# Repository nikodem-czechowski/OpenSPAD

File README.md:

# OpenSPAD
My implementation of the OpenSPAD based on the design by GaudiLabs

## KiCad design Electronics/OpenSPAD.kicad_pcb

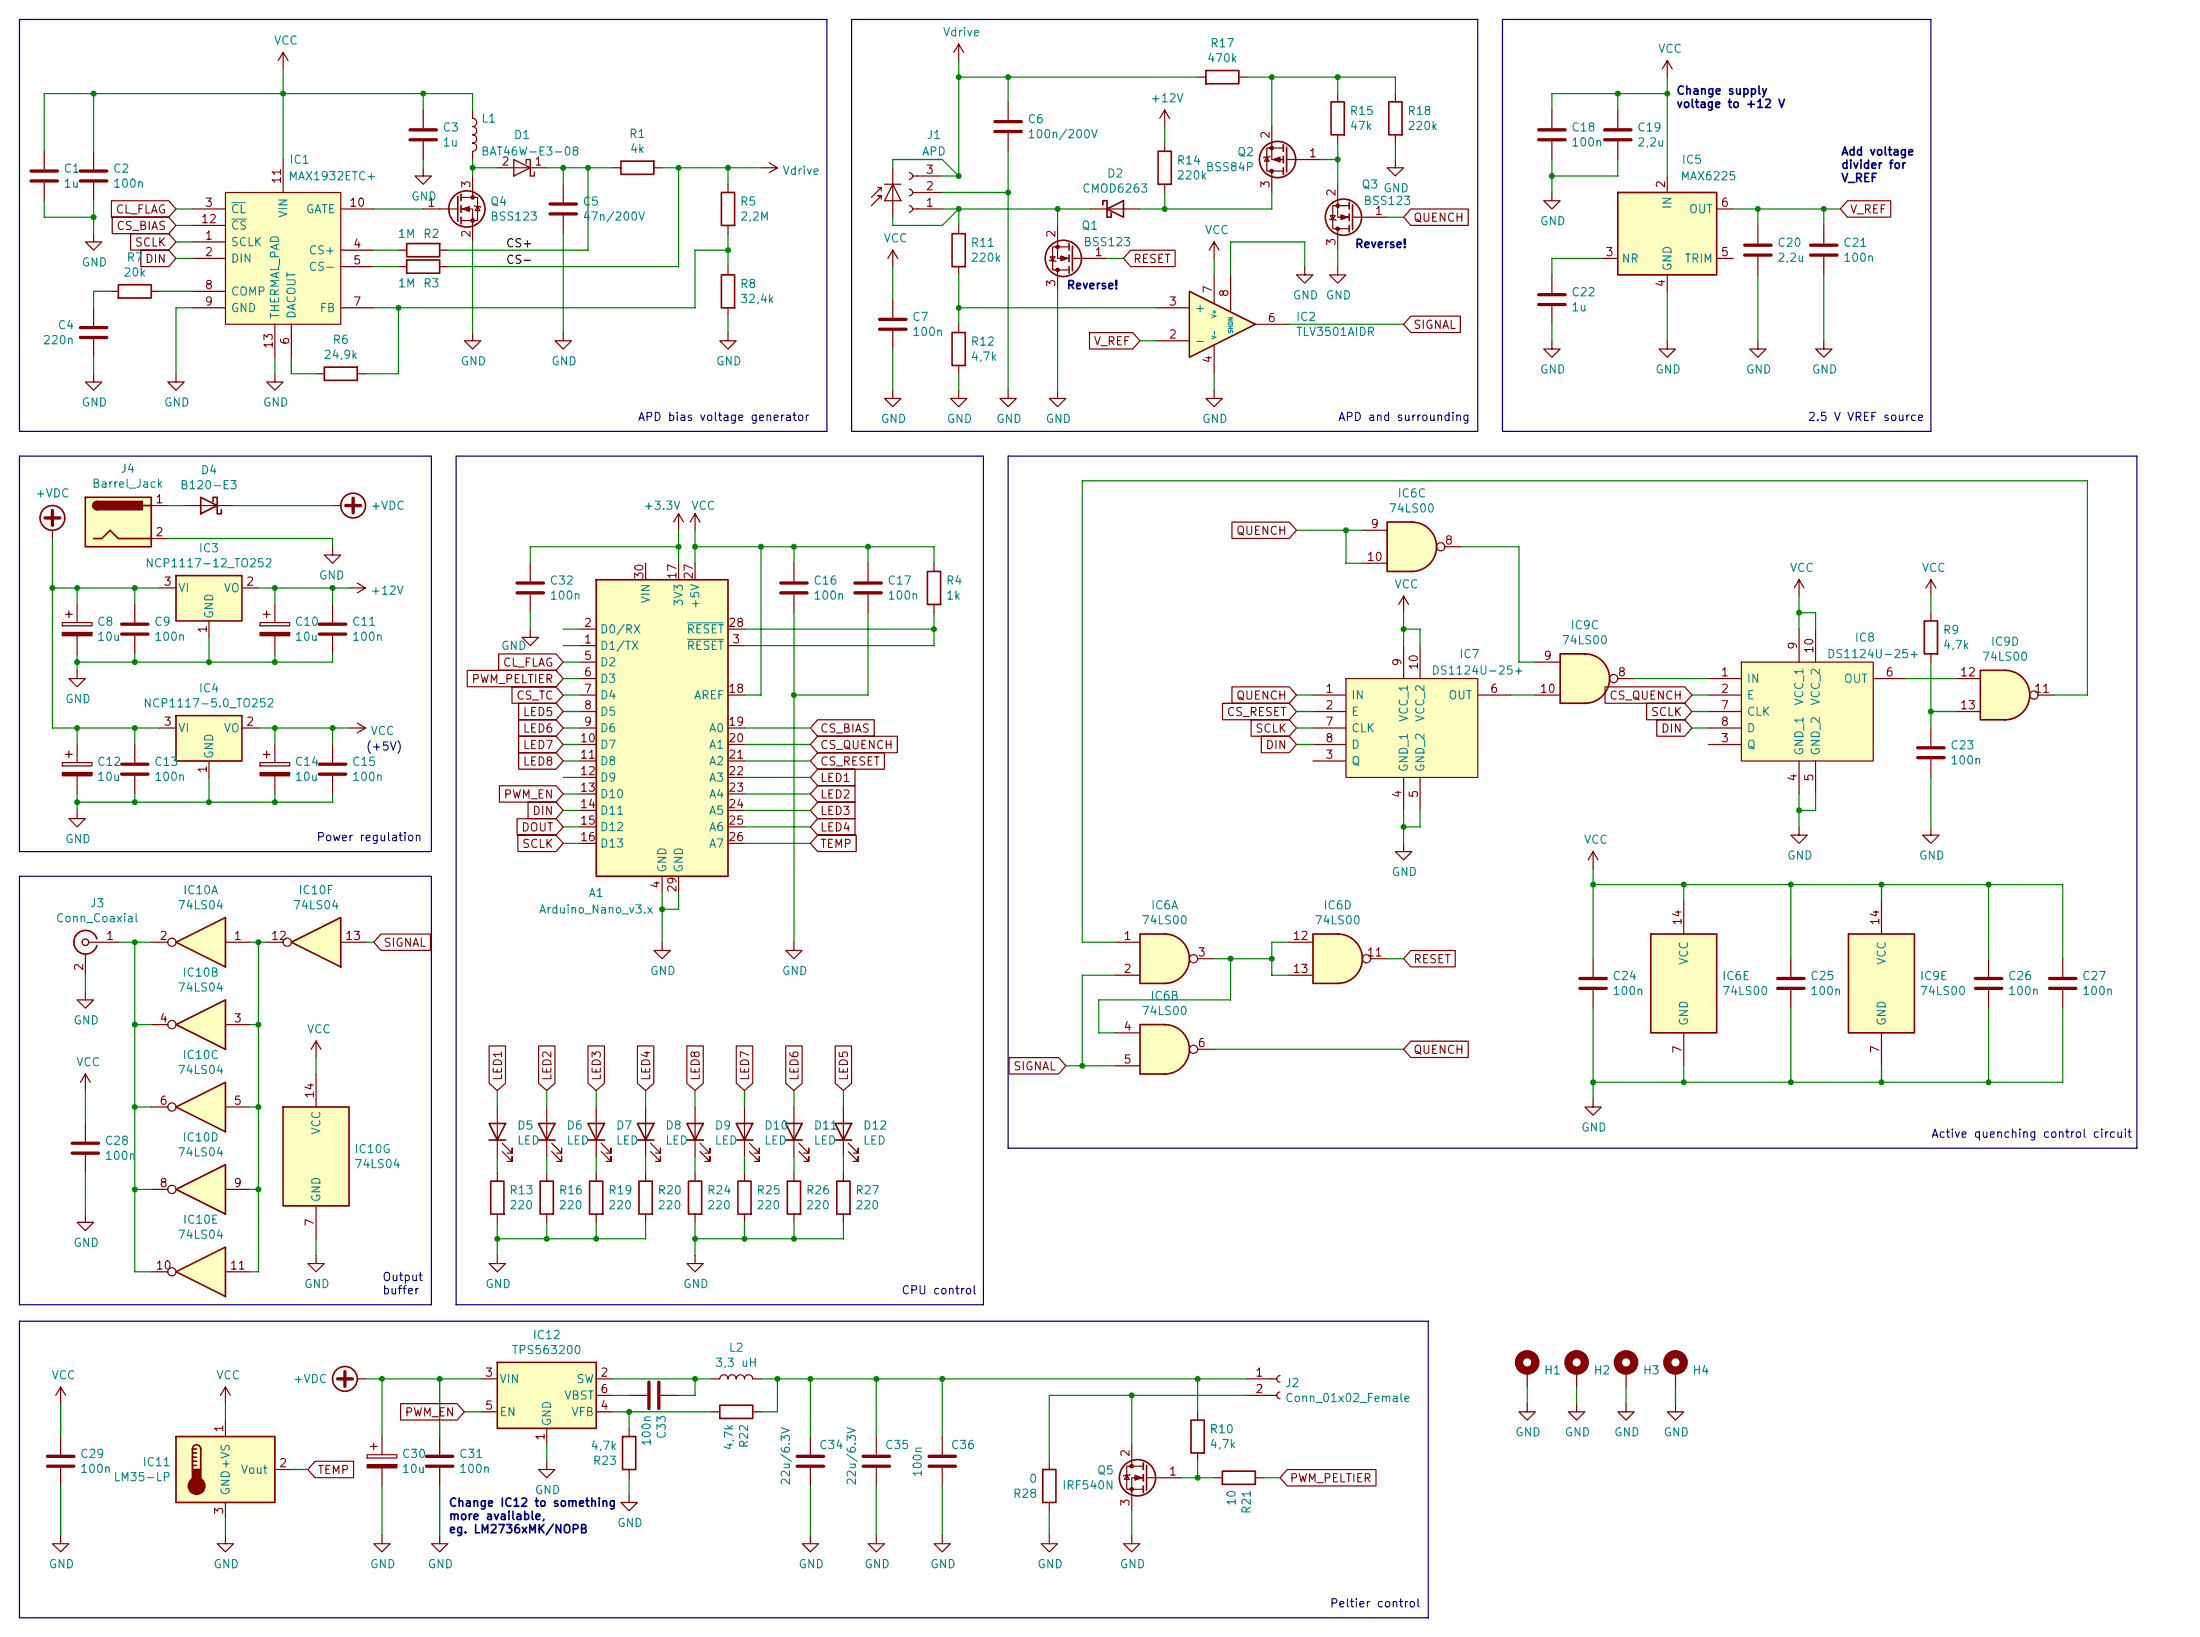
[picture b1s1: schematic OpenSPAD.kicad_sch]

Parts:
A1: Arduino_Nano_v3.x; Arduino_Nano
C1, C3, C22: 1u; C_1206_3216Metric
C2, C7, C9, C11, C13, C15, C16, C17, C18, C21, C23, C24, C25, C26, C27, C28, C29, C31, C32, C33, C36: 100n; C_1206_3216Metric
C4: 220n; C_1206_3216Metric
C5: 47n/200V; C_1206_3216Metric
C6: 100n/200V; C_1206_3216Metric
C8, C10, C12, C14, C30: 10u; C_Radial_D5.0mm_H11.0mm_P2.00mm
C19, C20: 2,2u; C_1206_3216Metric
C34, C35: 22u/6.3V; C_1206_3216Metric
D1: BAT46W-E3-08; SOD3716X135N; Mouser Part Number 78-BAT46W-E3-08
D2: CMOD6263; D_SOD-523
D3: BPX61; TO-5-2_Window
D4: B120-E3; D_SMA
D5, D6, D7, D8: LED; LED_0805_2012Metric
D9, D10, D11, D12: LED; LED_D3.0mm_Horizontal_O1.27mm_Z6.0mm
H1, H2, H3, H4: MountingHole_Pad; MountingHole_3.2mm_M3_Pad_Via
IC1: MAX1932ETC+; QFN80P400X400X80-13N-D; Manufacturer_Part_Number MAX1932ETC+; Mouser Part Number 700-MAX1932ETC
IC2: TLV3501AIDR; SOIC127P600X175-8N; Manufacturer_Part_Number TLV3501AIDR; Mouser Part Number 595-TLV3501AIDR
IC3: NCP1117-12_TO252; TO-252-2
IC4: NCP1117-5.0_TO252; TO-252-2
IC5: MAX6225; SOIC-8_3.9x4.9mm_P1.27mm
IC6, IC9: 74LS00; SOIC-14_3.9x8.7mm_P1.27mm
IC7, IC8: DS1124U-25+; SOP50P490X110-10N; Manufacturer_Part_Number DS1124U-25+
IC10: 74LS04; SOIC-14_3.9x8.7mm_P1.27mm
IC11: LM35-LP; TO-92_Inline
IC12: TPS563200; SOT-23-6
J1: APD; PinSocket_1x03_P2.54mm_Horizontal
J2: Conn_01x02_Female; PinHeader_1x02_P2.54mm_Vertical
J3: Conn_Coaxial; BNC_Amphenol_B6252HB-NPP3G-50_Horizontal
J4: Barrel_Jack; BarrelJack_CUI_PJ-102AH_Horizontal
L1: #A921CY-101M=P3; A921CY100MP3
L2: 3,3 uH; L_TDK_SLF7055
Q1, Q3, Q4: BSS123; SOT-23
Q2: BSS84P; SOT-23
Q5: IRF540N; TO-220-3_Horizontal_TabDown
R1: 4k; R_1206_3216Metric
R2, R3: 1M; R_1206_3216Metric
R4: 1k; R_1206_3216Metric
R5: 2,2M; R_1206_3216Metric
R6: 24,9k; R_1206_3216Metric
R7: 20k; R_1206_3216Metric
R8: 32,4k; R_1206_3216Metric
R9, R10, R12, R22, R23: 4,7k; R_1206_3216Metric
R11, R14, R18: 220k; R_1206_3216Metric
R13, R16, R19, R20, R24, R25, R26, R27: 220; R_0805_2012Metric
R15: 47k; R_1206_3216Metric
R17: 470k; R_1206_3216Metric
R21: 10; R_1206_3216Metric
R28: 0; R_1206_3216Metric

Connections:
+3V3: A1.17 (3V3), C32.1
+12V: C10.1, C11.1, IC3.2 (VO), R14.1
+VDC: C8.1, C9.1, C12.1, C13.1, C30.1, C31.1, D4.1 (K), IC3.3 (VI), IC4.3 (VI), IC12.3 (VIN)
/CS+: C5.2, D1.1, R1.1, R2.2
CL_FLAG: A1.5 (D2), IC1.3 (~CL)
CS_BIAS: A1.19 (A0), IC1.12 (~CS)
CS_QUENCH: A1.20 (A1), IC8.2 (E)
CS_RESET: A1.21 (A2), IC7.2 (E)
CS_TC: A1.7 (D4)
DIN: A1.14 (D11), IC1.2 (DIN), IC7.8 (D), IC8.8 (D)
DOUT: A1.15 (D12)
GND: A1.4 (GND), A1.29 (GND), C1.2, C2.2, C3.2, C4.1, C5.1, C6.1, C7.2, C8.2, C9.2, C10.2, C11.2, C12.2, C13.2, C14.2, C15.2, C16.2, C17.2, C18.2, C19.2, C20.2, C21.2, C22.2, C23.2, C24.2, C25.2, C26.2, C27.2, C28.2, C29.2, C30.2, C31.2, C32.2, C34.2, C35.2, C36.2, H1.1, H2.1, H3.1, H4.1, IC1.9 (GND), IC1.13 (THERMAL_PAD), IC2.4 (V-), IC2.8 (SHDN), IC3.1 (GND), IC4.1 (GND), IC5.4 (GND), IC6.7 (GND), IC7.4 (GND_1), IC7.5 (GND_2), IC8.4 (GND_1), IC8.5 (GND_2), IC9.7 (GND), IC10.7 (GND), IC11.3 (GND), IC12.1 (GND), J1.2, J3.2 (Ext), J4.2, Q1.3 (D), Q3.3 (D), Q4.2 (S), Q5.3 (S), R8.2, R12.2, R13.2, R16.2, R18.2, R19.2, R20.2, R23.1, R24.2, R25.2, R26.2, R27.2, R28.1
LED1: A1.22 (A3), D5.2 (A)
LED2: A1.23 (A4), D6.2 (A)
LED3: A1.24 (A5), D7.2 (A)
LED4: A1.25 (A6), D8.2 (A)
LED5: A1.8 (D5), D12.2 (A)
LED6: A1.9 (D6), D11.2 (A)
LED7: A1.10 (D7), D10.2 (A)
LED8: A1.11 (D8), D9.2 (A)
unnamed: A1.3 (~RESET), A1.28 (~RESET), R4.2
unnamed: C4.2, R7.2
unnamed: C22.1, IC5.3 (NR)
unnamed: C23.1, IC9.13, R9.2
unnamed: C33.1, IC12.2 (SW), L2.1
unnamed: C33.2, IC12.6 (VBST)
unnamed: C34.1, C35.1, C36.1, J2.1, L2.2, R10.1, R22.1
unnamed: D1.2, L1.2, Q4.3 (D)
unnamed: D2.1 (K), D3.1 (A), J1.1, Q1.2 (S), R11.1
unnamed: D2.2 (A), Q2.3 (D), R14.2
unnamed: D4.2 (A), J4.1
unnamed: D5.1 (K), R13.1
unnamed: D6.1 (K), R16.1
unnamed: D7.1 (K), R19.1
unnamed: D8.1 (K), R20.1
unnamed: D9.1 (K), R24.1
unnamed: D10.1 (K), R25.1
unnamed: D11.1 (K), R26.1
unnamed: D12.1 (K), R27.1
unnamed: IC1.4 (CS+), R2.1
unnamed: IC1.5 (CS-), R3.2
unnamed: IC1.6 (DACOUT), R6.1
unnamed: IC1.7 (FB), R5.2, R6.2, R8.1
unnamed: IC1.8 (COMP), R7.1
unnamed: IC1.10 (GATE), Q4.1 (G)
unnamed: IC2.3 (+), R11.2, R12.1
unnamed: IC6.1, IC9.11
unnamed: IC6.8, IC9.9
unnamed: IC6.3, IC6.4, IC6.12, IC6.13
unnamed: IC7.6 (OUT), IC9.10
unnamed: IC8.1 (IN), IC9.8
unnamed: IC8.6 (OUT), IC9.12
unnamed: IC10.1, IC10.3, IC10.5, IC10.9, IC10.11, IC10.12
unnamed: IC10.2, IC10.4, IC10.6, IC10.8, IC10.10, J3.1 (In)
unnamed: IC12.4 (VFB), R22.2, R23.2
unnamed: J2.2, Q5.2 (D), R28.2
unnamed: Q2.1 (G), Q3.2 (S), R15.2
unnamed: Q2.2 (S), R15.1, R17.1, R18.1
unnamed: Q5.1 (G), R10.2, R21.2
PWM_EN: A1.13 (D10), IC12.5 (EN)
PWM_PELTIER: A1.6 (D3), R21.1
QUENCH: IC6.6, IC6.9, IC6.10, IC7.1 (IN), Q3.1 (G)
RESET: IC6.11, Q1.1 (G)
SCLK: A1.16 (D13), IC1.1 (SCLK), IC7.7 (CLK), IC8.7 (CLK)
SIGNAL: IC2.6, IC6.2, IC6.5, IC10.13
TEMP: A1.26 (A7), IC11.2 (Vout)
VCC: A1.18 (AREF), A1.27 (+5V), C1.1, C2.1, C3.1, C7.1, C14.1, C15.1, C16.1, C17.1, C18.1, C19.1, C24.1, C25.1, C26.1, C27.1, C28.1, C29.1, IC1.11 (VIN), IC2.7 (V+), IC4.2 (VO), IC5.2 (IN), IC6.14 (VCC), IC7.9 (VCC_1), IC7.10 (VCC_2), IC8.9 (VCC_1), IC8.10 (VCC_2), IC9.14 (VCC), IC10.14 (VCC), IC11.1 (+VS), L1.1, R4.1, R9.1
V_REF: C20.1, C21.1, IC2.2 (-), IC5.6 (OUT)
Vdrive: C6.2, D3.2 (K), J1.3, R1.2, R3.1, R5.1, R17.2

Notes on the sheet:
2.5 V VREF source
APD and surrounding
CPU control
Peltier control
Reverse!
Add voltage divider for V_REF
(+5V)
Output buffer
Active quenching control circuit
Power regulation
Change supply voltage to +12 V
Change IC12 to something more available, eg. LM2736xMK/NOPB
APD bias voltage generator

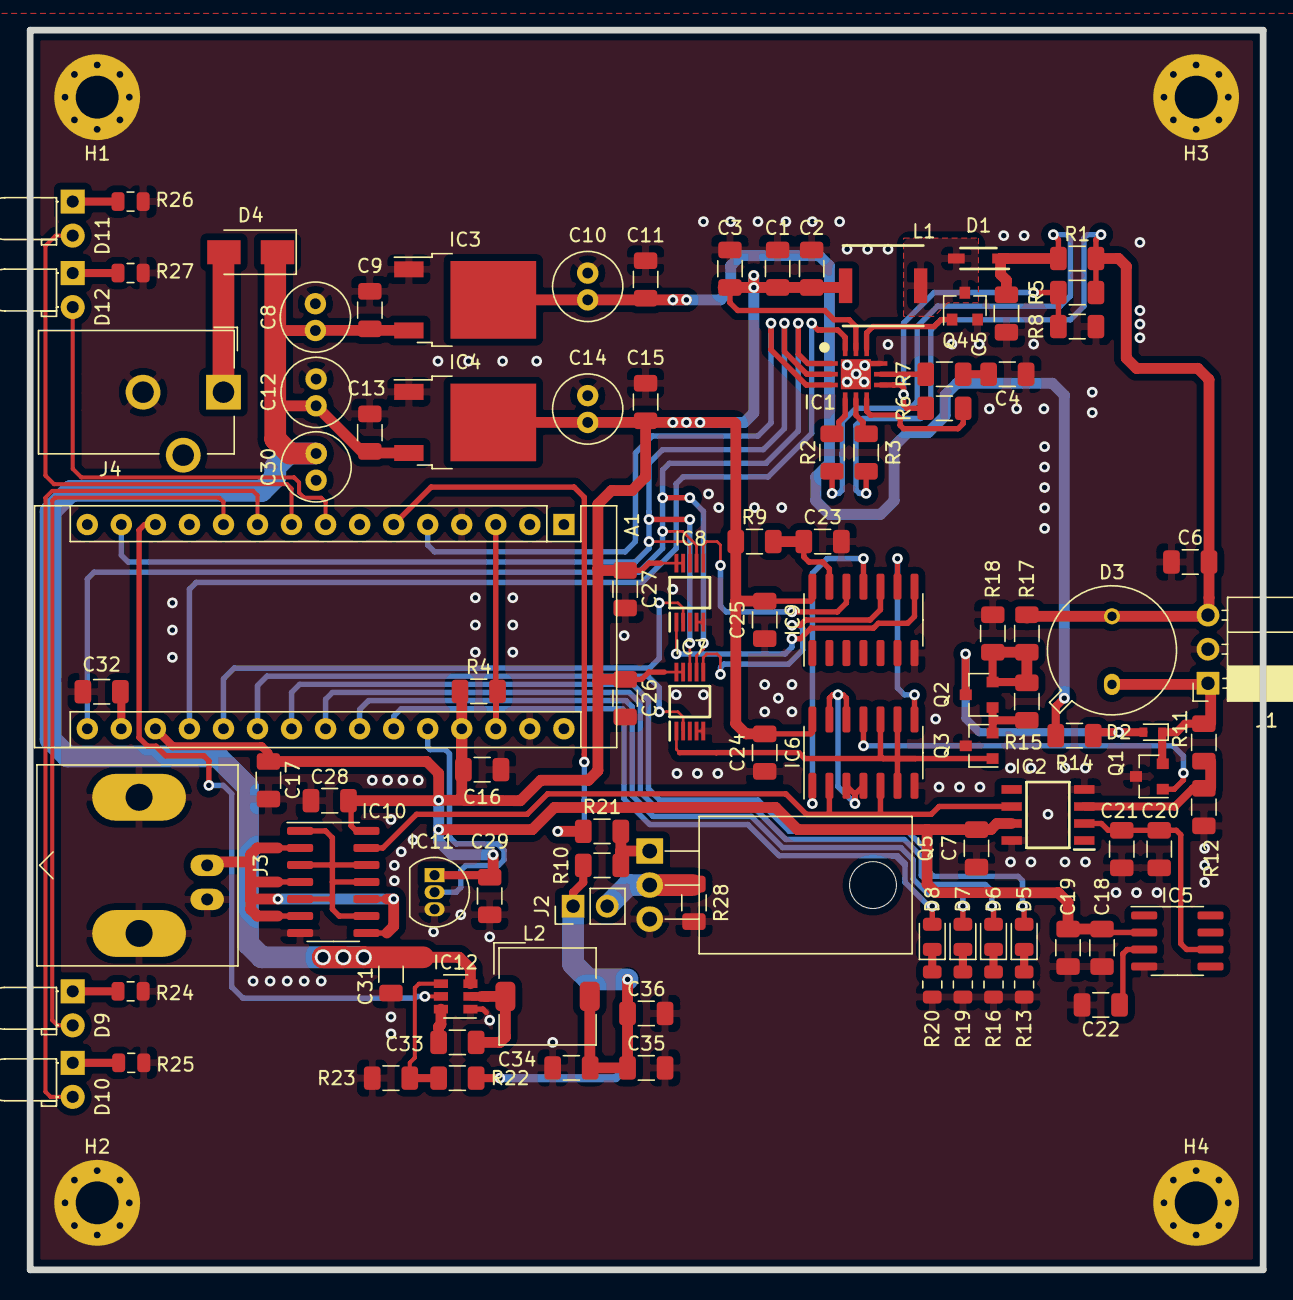
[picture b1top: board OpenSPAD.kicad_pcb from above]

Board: 2 copper layers, 92.0 x 92.5 mm, 104 parts (0 on the bottom side), 67 nets.

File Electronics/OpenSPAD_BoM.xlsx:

Id | Oznaczenie | Obudowa | Ilość | Oznaczenie | Dostawca i numer artykuĹ‚u |  | Do zamówienia
28 | A1 | Arduino_Nano | 1 | Arduino_Nano_v3.x |  |  | Nie
24 | C20,C19 | C_1206_3216Metric | 2 | 2,2u
23 | C22,C3,C1 | C_1206_3216Metric | 3 | 1u
17 | C30,C14,C12,C10,C8 | C_Radial_D5.0mm_H11.0mm_P2.00mm | 5 | 10u |  |  | NIE
4 | C31,C36,C33,C32,C29,C28,C27,C26,C25,C24,C23,C21,C18,C17,C16,C15,C13,C11,C9,C7,C2 | C_1206_3216Metric | 21 | 100n |  |  | Nie
8 | C35,C34 | C_1206_3216Metric | 2 | 22u/6.3V
48 | C4 | C_1206_3216Metric | 1 | 220n
47 | C5 | C_1206_3216Metric | 1 | 47n/200V
46 | C6 | C_1206_3216Metric | 1 | 100n/200V |  |  | NIE
13 | D1 | SOD3716X135N | 1 | BAT46W-E3-08
3 | D12,D11,D10,D9 | LED_D3.0mm_Horizontal_O1.27mm_Z6.0mm | 4 | LED
45 | D2 | D_SOD-523 | 1 | CMOD6263
44 | D3 | TO-5-2_Window | 1 | APD
25 | D4 | D_SMA | 1 | B120-E3
14 | D8,D7,D6,D5 | LED_0805_2012Metric | 4 | LED
12 | IC1 | QFN80P400X400X80-13N-D | 1 | MAX1932ETC+ |  |  | NIE
20 | IC10 | SOIC-14_3.9x8.7mm_P1.27mm | 1 | 74LS04 |  |  | NIE
19 | IC11 | TO-92_Inline | 1 | LM35-LP
5 | IC12 | SOT-23-6 | 1 | TPS562200 |  |  | NIE
11 | IC2 | SOIC127P600X175-8N | 1 | TLV3501AIDR |  |  | NIE
30 | IC3 | TO-252-2 | 1 | NCP1117-12_TO252 |  |  | NIE
29 | IC4 | TO-252-2 | 1 | NCP1117-5.0_TO252 |  |  | NIE
16 | IC5 | SOIC-8_3.9x4.9mm_P1.27mm | 1 | MAX6225 |  |  | NIE
10 | IC8,IC7 | SOP50P490X110-10N | 2 | DS1124U-25+ |  |  | NIE
21 | IC9,IC6 | SOIC-14_3.9x8.7mm_P1.27mm | 2 | 74LS00 |  |  | NIE
31 | J1 | PinSocket_1x03_P2.54mm_Horizontal | 1 | APD |  |  | 1
18 | J2 | PinHeader_1x02_P2.54mm_Vertical | 1 | Conn_01x02_Female
27 | J3 | BNC_Amphenol_B6252HB-NPP3G-50_Horizontal | 1 | Conn_Coaxial
26 | J4 | BarrelJack_CUI_PJ-102AH_Horizontal | 1 | Barrel_Jack |  |  | NIE
43 | L1 | A921CY100MP3 | 1 | #A921CY-101M=P3
7 | L2 | L_TDK_SLF7055 | 1 | 3,3 uH |  |  | NIE
42 | Q2 | SOT-23 | 1 | BSS84P
41 | Q4,Q3,Q1 | SOT-23 | 3 | BSS123
15 | Q5 | TO-220-3_Horizontal_TabDown | 1 | IRF540N
40 | R1 | R_1206_3216Metric | 1 | 4k
34 | R15 | R_1206_3216Metric | 1 | 47k
33 | R17 | R_1206_3216Metric | 1 | 470k
32 | R18,R14,R11 | R_1206_3216Metric | 3 | 220k
9 | R21 | R_1206_3216Metric | 1 | 10
6 | R23,R22,R10,R9,R12 | R_1206_3216Metric | 5 | 4,7k
2 | R27,R26,R25,R24,R20,R19,R16,R13 | R_0805_2012Metric | 8 | 220 |  |  | NIE
1 | R28 | R_1206_3216Metric | 1 | 0
39 | R3,R2 | R_1206_3216Metric | 2 | 1M
22 | R4 | R_1206_3216Metric | 1 | 1k |  |  | NIE
38 | R5 | R_1206_3216Metric | 1 | 2,2M
37 | R6 | R_1206_3216Metric | 1 | 24,9k
36 | R7 | R_1206_3216Metric | 1 | 20k
35 | R8 | R_1206_3216Metric | 1 | 32,4k

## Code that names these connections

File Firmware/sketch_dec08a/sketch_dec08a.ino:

#include <SPI.h>

#define VERSION 0.1

// SPI
#define SPI_DIN 11
#define SPI_DOUT 12
#define SPI_SCLK 13
#define SPI_CS_BIAS A0
#define SPI_CS_QUENCH A1
#define SPI_CS_RESET A2

// LED
#define LED1 A3 // inside
#define LED2 A4
#define LED3 A5
#define LED4 A6
#define LED5 5  // panel
#define LED6 6
#define LED7 7
#define LED8 9

// TC
#define TEMPERATURE A7
#define PELT_PWM 3

#define CL_FLAG 2

void setup() { // put your setup code here, to run once:
  Serial.begin(115200);
  Serial.println("Booting OpenSPAD");
  pinMode(CL_FLAG, INPUT);
  pinMode(LED1, OUTPUT);
  pinMode(LED2, OUTPUT);
  pinMode(LED3, OUTPUT);
  pinMode(LED4, OUTPUT);
  pinMode(LED5, OUTPUT);
  pinMode(LED6, OUTPUT);
  pinMode(LED7, OUTPUT);
  pinMode(LED8, OUTPUT);
  digitalWrite(LED5, 1);
  pinMode(SPI_CS_BIAS, OUTPUT);
  digitalWrite(SPI_CS_BIAS, 1);
  pinMode(SPI_CS_QUENCH, OUTPUT);
  digitalWrite(SPI_CS_QUENCH, 0);
  pinMode(SPI_CS_RESET, OUTPUT);
  digitalWrite(SPI_CS_RESET, 0);
  pinMode(PELT_PWM, OUTPUT);
  // analogWrite(PELT_PWM, 0);
  digitalWrite(PELT_PWM, 0);
  Serial.print("Firmware version: ");
  Serial.println(VERSION);
  delay(500);
  SPI.begin();
  SPI.setClockDivider(SPI_CLOCK_DIV16); // Clock = masterclock / 8 = 16 MHz / 8 = 2 MHz (DS1124 is max 10 MHz, MAX1932 is max 2 MHz)
  SPI.setDataMode(SPI_MODE0);
  SPI.setBitOrder(MSBFIRST);
  digitalWrite(LED5, 0);
  digitalWrite(LED6, 1);

  digitalWrite(SPI_CS_BIAS, 0);
  SPI.transfer(00);
  digitalWrite(SPI_CS_BIAS, 1);
}

byte n = 0;

void loop() { // put your main code here, to run repeatedly:
//  digitalWrite(SPI_CS_RESET, 1);
//  SPI.transfer(n);
//  digitalWrite(SPI_CS_RESET, 0);
//  digitalWrite(SPI_CS_QUENCH, 1);
//  SPI.transfer(n);
//  digitalWrite(SPI_CS_QUENCH, 0);
  digitalWrite(SPI_CS_BIAS, 0);
  SPI.transfer(n);
  digitalWrite(SPI_CS_BIAS, 1);
  // Serial.print("Set value: ");
  // Serial.println(String(n));
  // delay(1); 
  n++;
  if(n>255){
    n = 0;
  }
}
